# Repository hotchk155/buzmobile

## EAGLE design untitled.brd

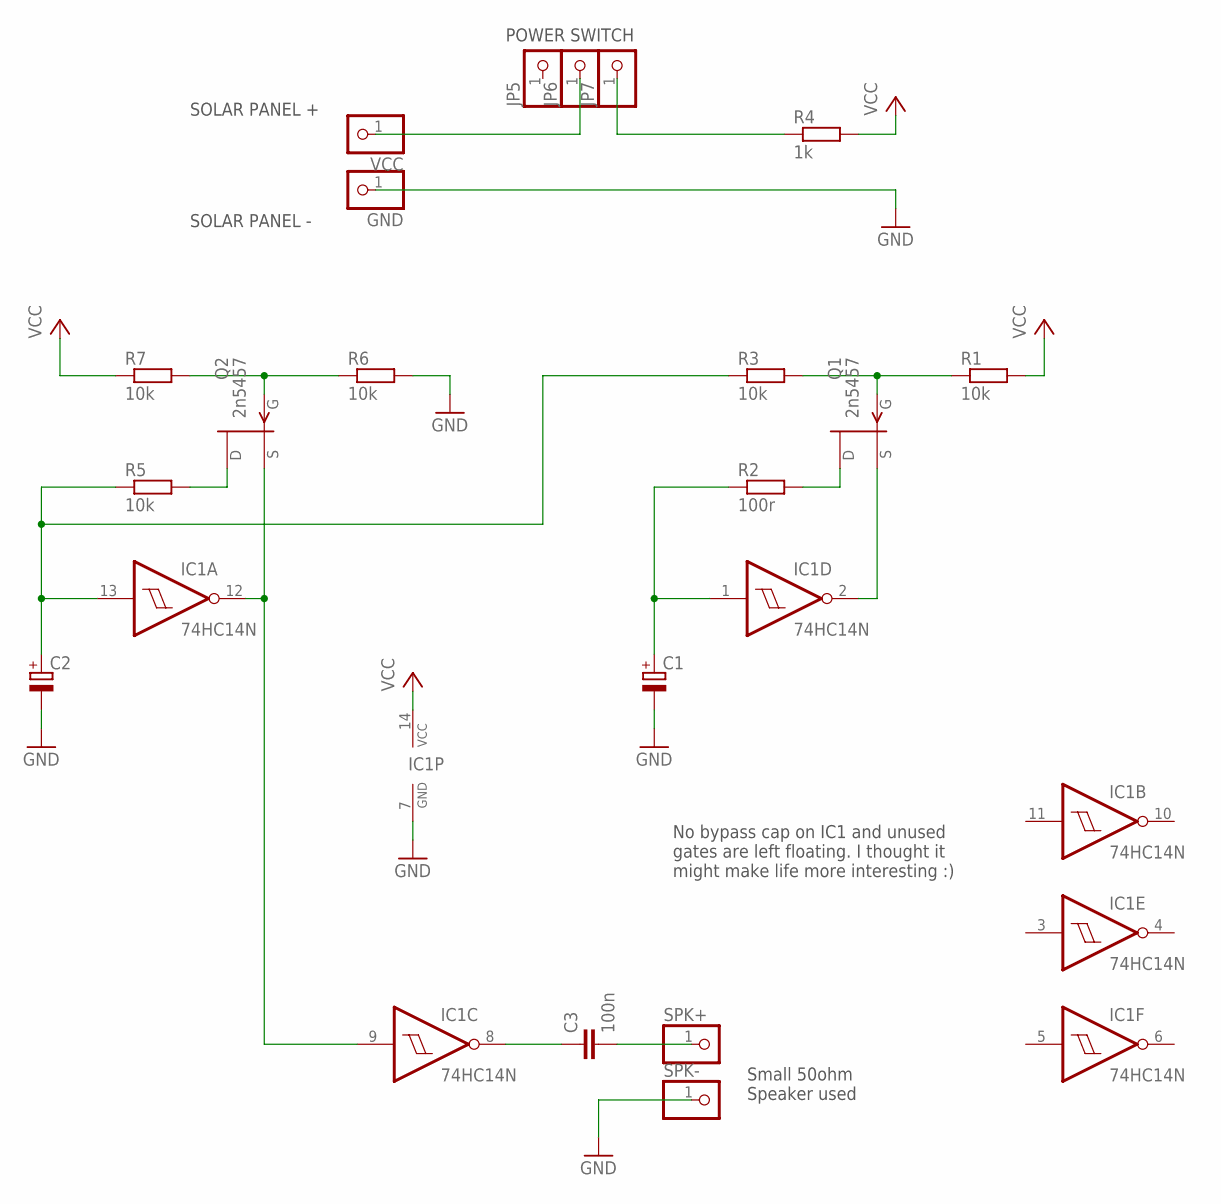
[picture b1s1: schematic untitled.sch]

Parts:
C1, C2: CPOL-EUE2.5-5; E2,5-5
C3: 100n; C025-025X050
GND: PINHD-1X1; 1X01
IC1: 74HC14N; DIL14
JP5, JP6, JP7: PINHD-1X1; 1X01
Q1, Q2: 2n5457; TO92-
R1, R3, R5, R6, R7: 10k; 0207/10
R2: 100r; 0207/10
R4: 1k; 0207/10
SPK+: PINHD-1X1; 1X01
SPK-: PINHD-1X1; 1X01
VCC: PINHD-1X1; 1X01

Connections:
GND: C1.-, C2.-, GND.1, IC1.7 (GND), R6.2, SPK-.1
unnamed: C2.+, IC1.13 (I), R3.1, R5.1
unnamed: JP6.1, VCC.1
unnamed: Q2.3 (D), R5.2
unnamed: IC1.9 (I), IC1.12 (O), Q2.2 (S)
unnamed: Q2.1 (G), R6.1, R7.2
unnamed: C1.+, IC1.1 (I), R2.1
unnamed: Q1.3 (D), R2.2
unnamed: IC1.2 (O), Q1.2 (S)
unnamed: Q1.1 (G), R1.1, R3.2
unnamed: JP7.1, R4.1
unnamed: C3.1, IC1.8 (O)
SPK: C3.2, SPK+.1
VCC: IC1.14 (VCC), R1.2, R4.2, R7.1

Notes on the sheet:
POWER SWITCH
SOLAR PANEL +
SOLAR PANEL -
No bypass cap on IC1 and unused gates are left floating. I thought it might make life more interesting :)
Small 50ohm Speaker used

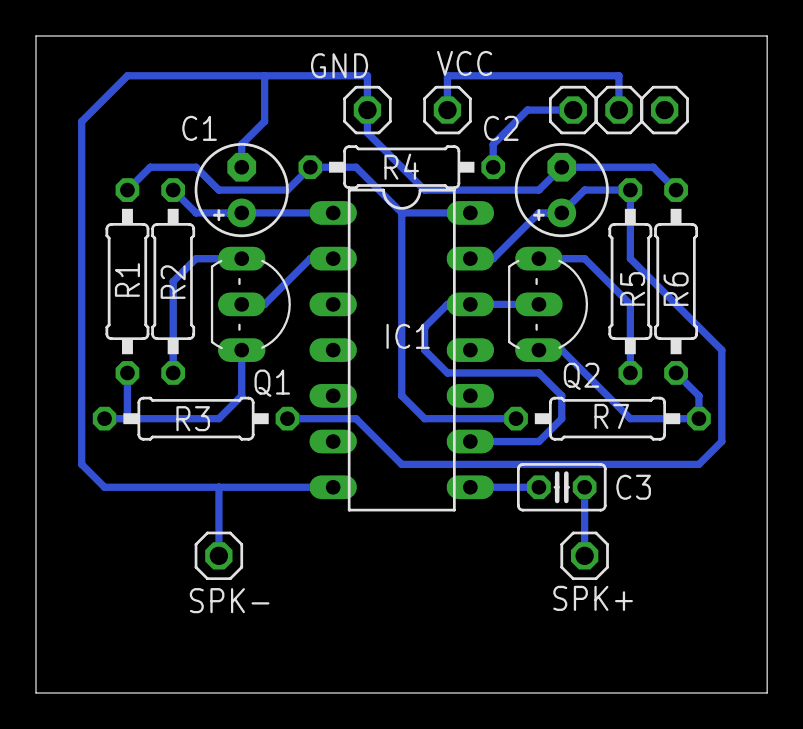
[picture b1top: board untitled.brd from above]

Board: 2 copper layers, 40.6 x 36.5 mm, 20 parts (0 on the bottom side), 14 nets.

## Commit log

2022-08-24 images
2022-08-24 saas
